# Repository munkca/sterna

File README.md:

# sterna
30-key hot-swap wireless keyboard based on the Tern.

This is my remodeled and personalized [Tern](https://github.com/rschenk/tern/)/[tern-ble](https://gitlab.com/gleb_sexy/tern-ble/) adapted to my personal preferences. I used this adaptation as a means to get familiar with Ergogen and kiCAD.

Differences from the Tern/Tern-ble:
- choc-spacing (17.5 x 16.5 mm)
- more splay and stagger
- wireless
- on/off switch
- reset button
- bottom case with acrylic keyplate

## Warning
This is an untested work in progress. I will let you know once I have built and tested this keyboard.

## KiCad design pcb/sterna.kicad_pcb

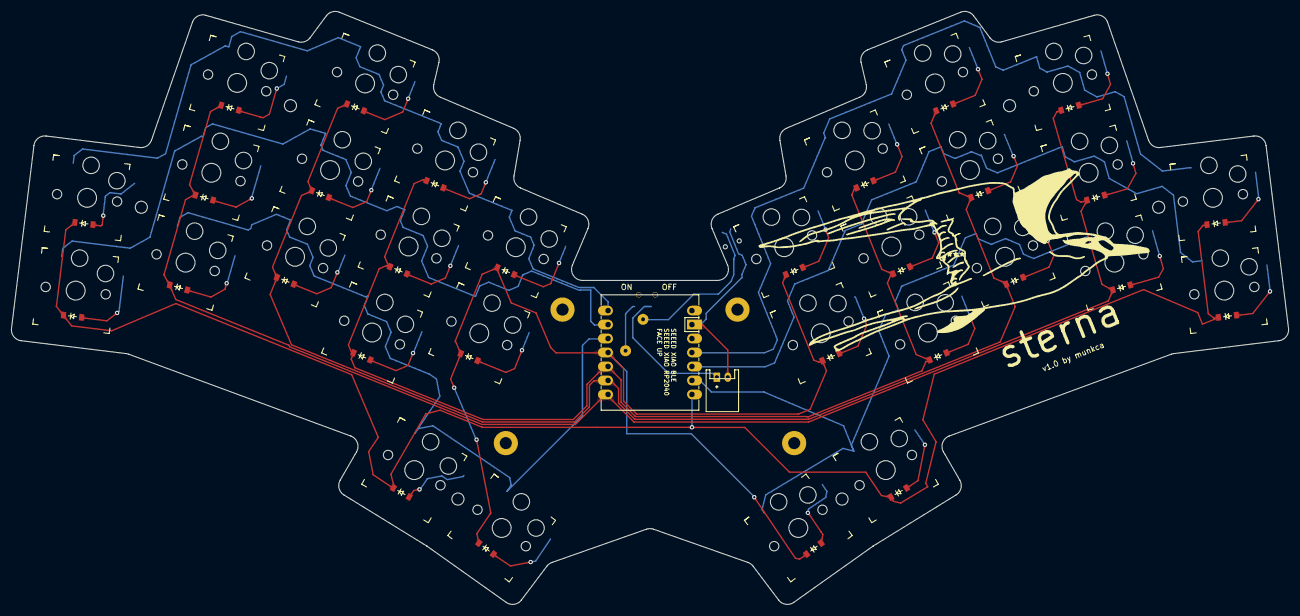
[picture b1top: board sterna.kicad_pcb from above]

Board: 2 copper layers, 232.3 x 107.8 mm, 74 parts (1 on the bottom side), 45 nets.

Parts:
B1: Panasonic_EVQPUL_EVQPUC
D1, D2, D3, D4, D5, D6, D7, D8, D9, D10, D11, D12, D13, D14, D15, D16, D17, D18, D19, D20, D21, D22, D23, D24, D25, D26, D27, D28, D29, D30: ComboDiode
JST1: JST_PH_S2B-PH-K_02x2.00mm_Angled
MCU1: xiao-ble
PAD1, PAD2, PAD3, PAD4: MountingHole_2.2mm_M2_Pad
PAD5, PAD6, PAD7, PAD8, PAD9, PAD10: MountingHole_2.2mm_M2
S1, S2, S3, S4, S5, S6, S7, S8, S9, S10, S11, S12, S13, S14, S15, S16, S17, S18, S19, S20, S21, S22, S23, S24, S25, S26, S27, S28, S29, S30: Kailh_socket_PG1350
T1: SPDT_C128955

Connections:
BAT+: MCU1.19, T1.1
BAT_POS: JST1.1, T1.2
C0: D12.1, D13.1, D25.1, D26.1, D28.1, D30.1, MCU1.4
C1: D9.1, D10.1, D11.1, D22.1, D23.1, D24.1, MCU1.5
C2: D6.1, D7.1, D8.1, D19.1, D20.1, D21.1, MCU1.6
C3: D3.1, D4.1, D5.1, D16.1, D17.1, D18.1, MCU1.7
C4: D1.1, D2.1, D14.1, D15.1, D27.1, D29.1, MCU1.8
GND: B1.2, JST1.2, MCU1.13
R0: MCU1.1, S2.1, S5.1, S8.1, S11.1, S13.1
R1: MCU1.2, S1.1, S4.1, S7.1, S10.1, S12.1
R2: MCU1.3, S3.1, S6.1, S9.1, S27.1, S28.1
R3: MCU1.9, S16.1, S19.1, S22.1, S29.1, S30.1
R4: MCU1.10, S14.1, S17.1, S20.1, S23.1, S25.1
R5: MCU1.11, S15.1, S18.1, S21.1, S24.1, S26.1
RST: B1.1, MCU1.17
home_thumb: D27.2, S27.2
index_bottom: D9.2, S9.2
index_home: D10.2, S10.2
index_top: D11.2, S11.2
inner_home: D12.2, S12.2
inner_top: D13.2, S13.2
middle_bottom: D6.2, S6.2
middle_home: D7.2, S7.2
middle_top: D8.2, S8.2
mirror_home_thumb: D29.2, S29.2
mirror_index_bottom: D22.2, S22.2
mirror_index_home: D23.2, S23.2
mirror_index_top: D24.2, S24.2
mirror_inner_home: D25.2, S25.2
mirror_inner_top: D26.2, S26.2
mirror_middle_bottom: D19.2, S19.2
mirror_middle_home: D20.2, S20.2
mirror_middle_top: D21.2, S21.2
mirror_pinky_bottom: D14.2, S14.2
mirror_pinky_home: D15.2, S15.2
mirror_reachy_thumb: D30.2, S30.2
mirror_ring_bottom: D16.2, S16.2
mirror_ring_home: D17.2, S17.2
mirror_ring_top: D18.2, S18.2
pinky_bottom: D1.2, S1.2
pinky_home: D2.2, S2.2
reachy_thumb: D28.2, S28.2
ring_bottom: D3.2, S3.2
ring_home: D4.2, S4.2
ring_top: D5.2, S5.2

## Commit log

2025-10-18 Add M2 mounting hole footprint definition
2025-10-18 Add button_side_push footprint module
2025-10-18 Rename hole_m2 to hole_m2.js
2025-10-18 Add MCU cover mounting hole footprint module
2025-10-18 Add case wall thickness and define case1 structure
2025-10-18 Refactor config.yaml for edge border and holes
    Updated edge border size and modified mounting hole definitions. Removed unused case definitions and adjusted keycap and switch hole references.
2025-10-21 Add cases section to config.yaml
2025-10-21 Create empty-file
2025-10-21 Create test
2025-10-25 Rename sterna.kicad_pcb to pcb/sterna.kicad_pcb
2025-10-25 Rename sterna.kicad_prl to pcb/sterna.kicad_prl
2025-10-25 Rename sterna.kicad_pro to pcb/sterna.kicad_pro
2025-10-25 Create blank
2025-10-26 Rename firmware/zmk/sterna.conf to firmware/zmk/boards/shields/sterna.conf
2025-10-26 Rename firmware/zmk/boards/shields/sterna.conf to firmware/zmk/boards/shields/sterna/sterna.conf
2025-10-26 Create build.yaml for board and shield setup
    Add build configuration for GitHub Actions matrix
2025-10-26 Rename tern-layouts.dtsi to sterna-layouts.dtsi
2025-10-26 Rename tern.keymap to sterna.keymap
